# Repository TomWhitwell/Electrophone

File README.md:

# Electrophone

Electrophone is a Eurorack module containing a full-sized single coil guitar pickup.  

This module is a sister to the Mikrophonie Contact Mic Module and Magnetophone Tape Head Module. The Mikrophonie picks up physical vibrations, while Electrophone can hear electromagnetic vibrations. Guitar pickups are designed to convert vibrating metal (strings) into audio, but single coil pickups are also notoriously susceptible to interference of all kinds; hum from transformers, fluorescent lights or even radio signals.

This module is named after the [Epiphone Electrophone](http://www.oldfrets.com/Electrophone.html) an electric guitar from 1935.  

More information: 
- [FAQ](https://github.com/TomWhitwell/Electrophone/wiki/Music-Thing-Electrophone:-FAQ) 
- [BOM](https://github.com/TomWhitwell/Electrophone/wiki/Music-Thing-Elecrophone:-BOM)
- [Troubleshooting](https://github.com/TomWhitwell/Electrophone/wiki/Music-Thing-Electrophone:-Troubleshooting)
- [Demo video at Superbooth 16](https://youtu.be/UVMrQejVZlw?t=3m17s)

Status:  
- August 2016: Finalised circuit 
- May 2016: revised Rev 4 layout trying to get the fuzz circuit to work 
- March 2016: Demonstrated at Superbooth16 in Berlin, with Fuzz circuit bypassed. 
- December 2015: Small component changes in Pickup Board. 
- November 2015: Minor fault in Panel (pickup cutout slightly tight) and major faults in Pickup Board. Rev2 board designed and sent to fab.  
- October 2015: Rev 1 prototype boards sent to fab

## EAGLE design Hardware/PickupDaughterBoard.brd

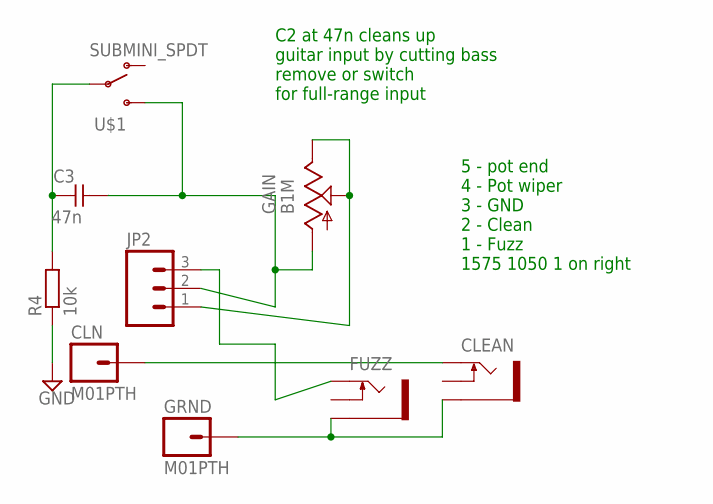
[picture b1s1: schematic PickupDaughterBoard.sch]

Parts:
C3: 47n; C050-024X044
CLEAN: THONKICONNNEW; WQP-PJ301M-12_JACK
CLN: M01PTH; 1X01
FUZZ: THONKICONNNEW; WQP-PJ301M-12_JACK
GAIN: B1M; EVUF
GRND: M01PTH; 1X01
JP2: M03PTH; 1X03
R4: 10k; VERTICAL_RESISTOR
U$1: SUBMINI_SPDT; SUBMINI_TOGGLE

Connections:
CLEAN: CLEAN.P$1_TIP (TIP), CLN.1
END: C3.1, GAIN.1 (A), JP2.2, U$1.3 (S)
FUZZ: FUZZ.P$1_TIP (TIP), JP2.3
GND: CLEAN.P$3_SLEEVE (SLEEVE), FUZZ.P$3_SLEEVE (SLEEVE), GRND.1, R4.1
unnamed: C3.2, R4.2, U$1.COM (COMMON)
WIPER: GAIN.2 (S), GAIN.3 (E), JP2.1

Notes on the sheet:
5 - pot end 4 - Pot wiper 3 - GND 2 - Clean 1 - Fuzz 1575 1050 1 on right
C2 at 47n cleans up guitar input by cutting bass remove or switch for full-range input

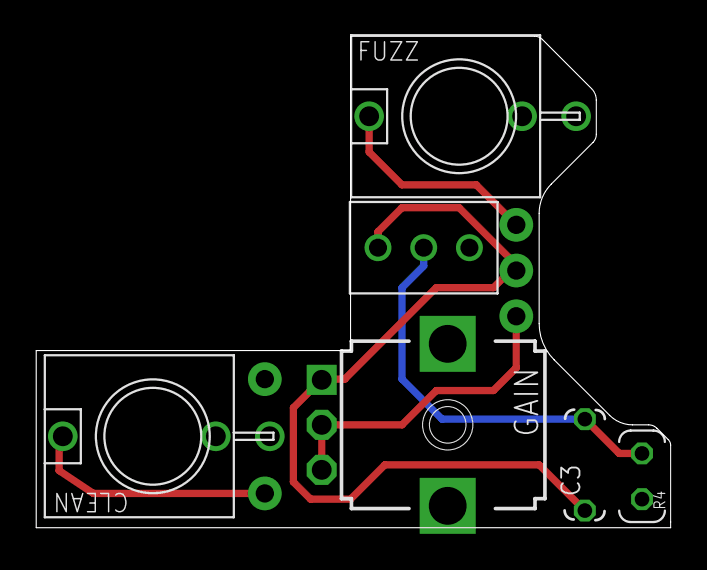
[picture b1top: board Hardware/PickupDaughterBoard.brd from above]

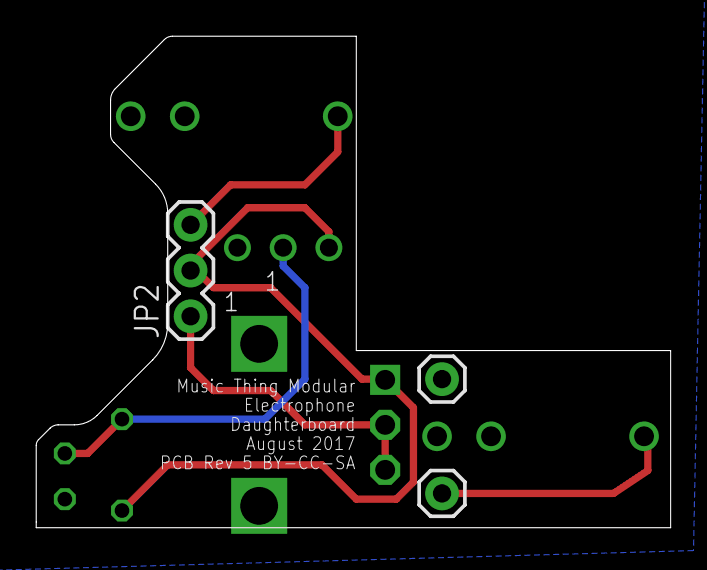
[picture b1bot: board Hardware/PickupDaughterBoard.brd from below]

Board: 2 copper layers, 35.2 x 27.3 mm, 9 parts (3 on the bottom side), 6 nets.

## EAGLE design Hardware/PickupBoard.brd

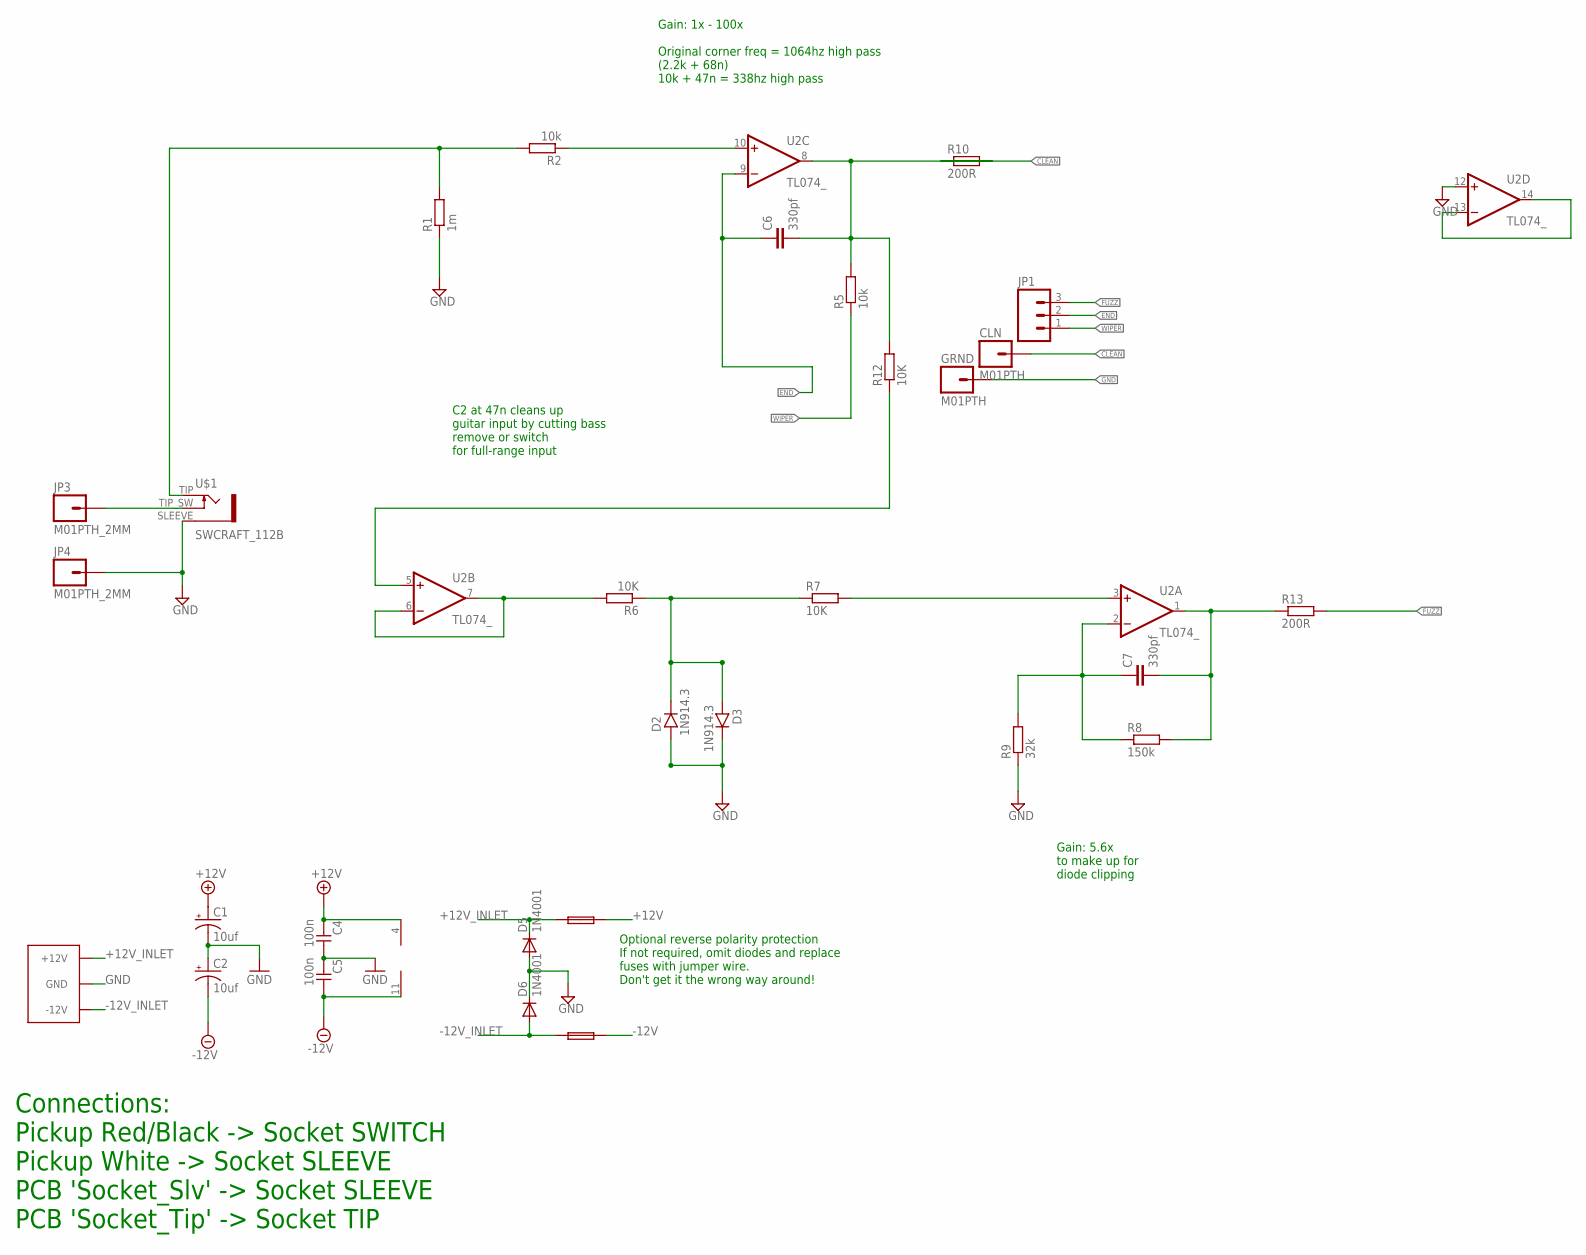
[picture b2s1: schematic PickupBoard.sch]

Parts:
1: FUSE; C050H075X075
C1, C2: 10uf; CPOL-RADIAL-10UF-25V
C4, C5: 100n; C050-024X044
C6, C7: 330pf; 050X030_025
CLN: M01PTH; 1X01
D2, D3: 1N914.3; DO35-3
D5, D6: 1N4001; DO41-10
FUSE: FUSE; C050H075X075
GRND: M01PTH; 1X01
JP1: M03PTH; 1X03
JP3, JP4: M01PTH_2MM; 1X01_2MM
R1: 1m; 7MM_RESISTOR
R2, R5: 10k; 7MM_RESISTOR
R6, R7, R12: 10K; 7MM_RESISTOR
R8: 150k; 7MM_RESISTOR
R9: 32k; 7MM_RESISTOR
R10, R13: 200R; 7MM_RESISTOR
U2: TL074_; DIL14
U$1: SWCRAFT_112B; SWCRAFT_112_SLOTS
U$2: EURO_POWER_LOCK; EURO_PWR_HEADER_LOCK

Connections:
+12V: 1.2, C1.1 (+), C4.2, U2.4 (V+)
+12V_INLET: 1.1, D5.C, U$2.POS1 (+12V), U$2.POS2 (+12V)
-12V: C2.2 (-), C5.1, FUSE.2, U2.11 (V-)
-12V_INLET: D6.A, FUSE.1, U$2.NEG1 (-12V), U$2.NEG2 (-12V)
CLEAN: CLN.1, R10.1
END: C6.1, JP1.2, U2.9 (-IN)
FUZZ: JP1.3, R13.2
GAIN_IN: R1.2, R2.2, U$1.TIP (3)
GND: C1.2 (-), C2.1 (+), C4.1, C5.2, D2.A, D3.C, D5.A, D6.C, GRND.1, JP4.1, R1.1, R9.1, U2.12 (+IN), U$1.SLEEVE (5), U$2.GND1 (GND), U$2.GND2 (GND), U$2.GND3 (GND), U$2.GND4 (GND), U$2.GND5 (GND), U$2.GND6 (GND)
unnamed: R2.1, U2.10 (+IN)
unnamed: U2.13 (-IN), U2.14 (OUT)
unnamed: R7.2, U2.3 (+IN)
unnamed: D2.C, D3.A, R6.1, R7.1
unnamed: C7.1, R8.1, R9.2, U2.2 (-IN)
unnamed: C7.2, R8.2, R13.1, U2.1 (OUT)
unnamed: JP3.1, U$1.TIP_SW (4)
unnamed: C6.2, R5.2, R10.2, R12.2, U2.8 (OUT)
unnamed: R12.1, U2.5 (+IN)
unnamed: R6.2, U2.6 (-IN), U2.7 (OUT)
WIPER: JP1.1, R5.1

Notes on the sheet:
Optional reverse polarity protection If not required, omit diodes and replace fuses with jumper wire. Don't get it the wrong way around!
Connections: Pickup Red/Black -> Socket SWITCH Pickup White -> Socket SLEEVE PCB 'Socket_Slv' -> Socket SLEEVE PCB 'Socket_Tip' -> Socket TIP
Gain: 1x - 100x Original corner freq = 1064hz high pass (2.2k + 68n) 10k + 47n = 338hz high pass
Gain: 5.6x to make up for diode clipping
C2 at 47n cleans up guitar input by cutting bass remove or switch for full-range input

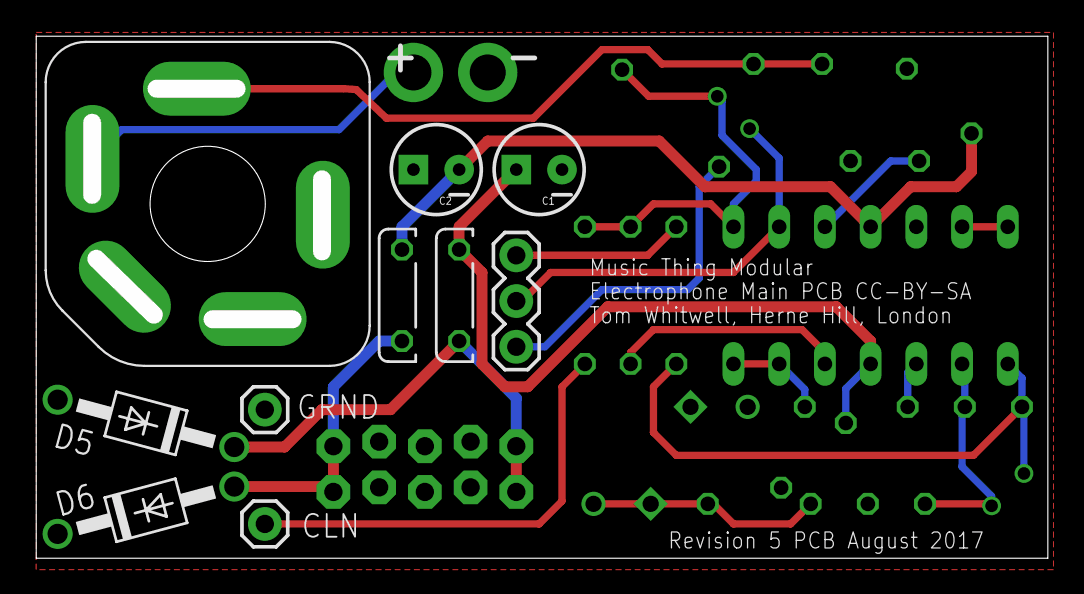
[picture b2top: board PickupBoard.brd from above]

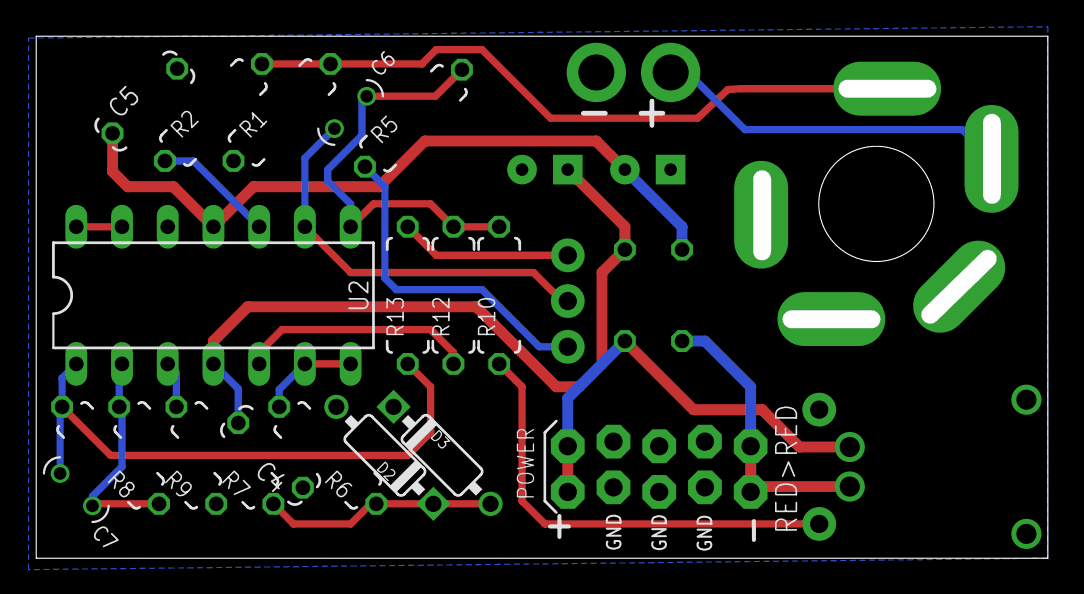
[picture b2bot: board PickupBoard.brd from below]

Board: 4 copper layers, 55.2 x 28.0 mm, 30 parts (20 on the bottom side), 20 nets.

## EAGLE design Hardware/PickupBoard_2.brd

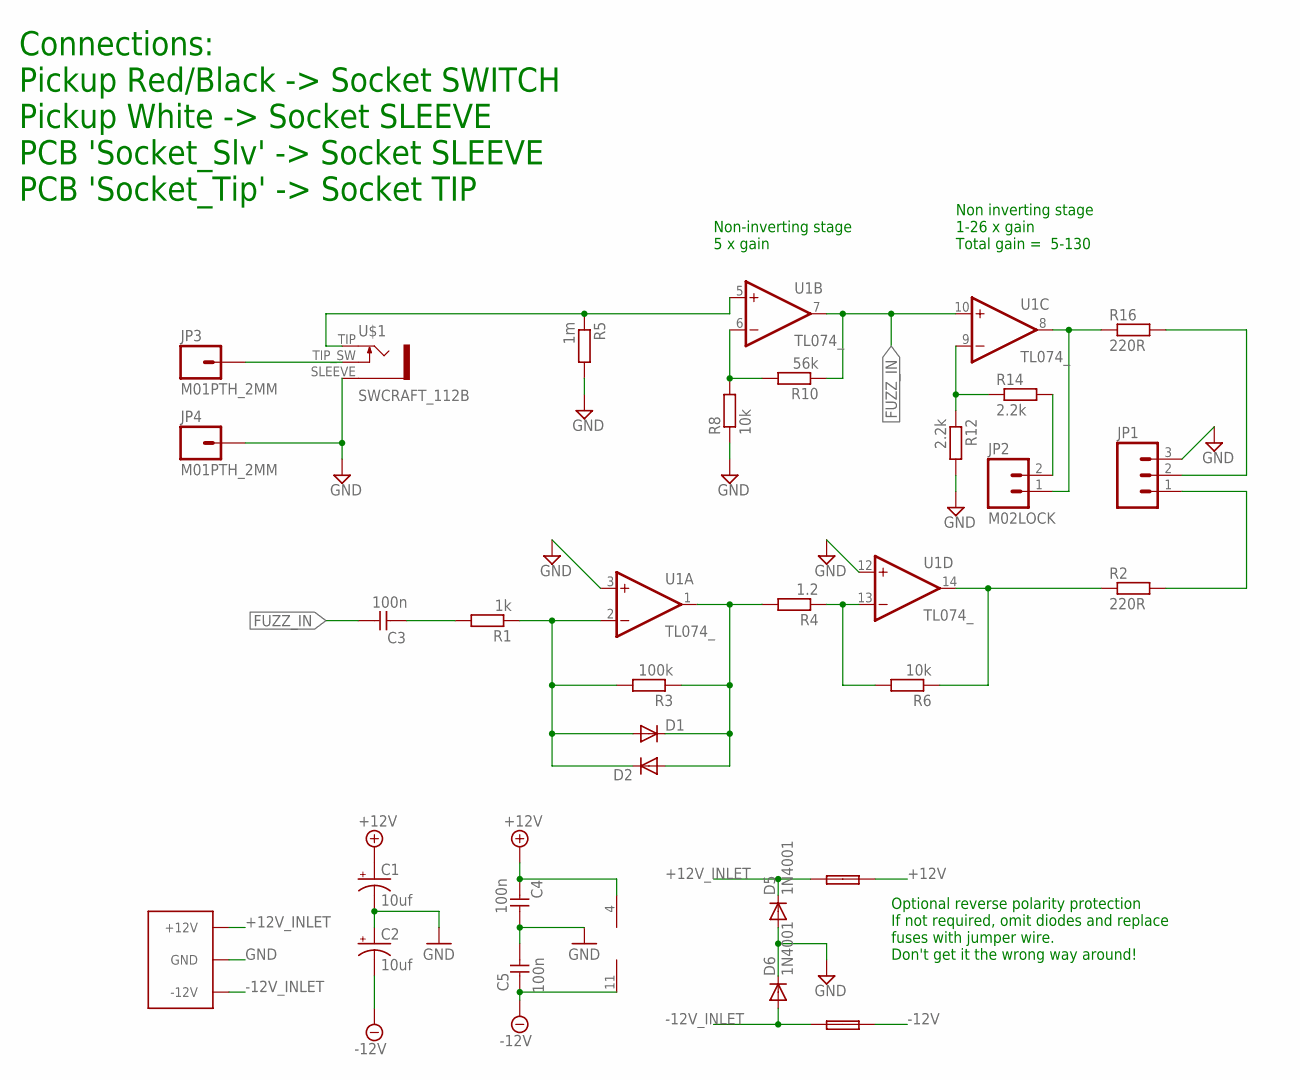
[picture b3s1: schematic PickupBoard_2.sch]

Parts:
1: FUSE; C050H075X075
C1, C2: 10uf; CPOL-RADIAL-10UF-25V
C3, C4, C5: 100n; C050-024X044
D1, D2: SMALL_DIODEDO35-7; DO35-7
D5, D6: 1N4001; DO41-10
FUSE: FUSE; C050H075X075
JP1: M03LOCK; 1X03_LOCK
JP2: M02LOCK; 1X02_LOCK
JP3, JP4: M01PTH_2MM; 1X01_2MM
R1: 1k; 7MM_RESISTOR
R2, R16: 220R; 7MM_RESISTOR
R3: 100k; 7MM_RESISTOR
R4: 1.2; 7MM_RESISTOR
R5: 1m; 7MM_RESISTOR
R6, R8: 10k; 7MM_RESISTOR
R10: 56k; 7MM_RESISTOR
R12, R14: 2.2k; 7MM_RESISTOR
U1: TL074_; DIL14
U$1: SWCRAFT_112B; SWCRAFT_112_SLOTS
U$2: EURO_POWER_LOCK; EURO_PWR_HEADER_LOCK

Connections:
+12V: 1.2, C1.1 (+), C4.2, U1.4 (V+)
+12V_INLET: 1.1, D5.C, U$2.POS1 (+12V), U$2.POS2 (+12V)
-12V: C2.2 (-), C5.2, FUSE.2, U1.11 (V-)
-12V_INLET: D6.A, FUSE.1, U$2.NEG1 (-12V), U$2.NEG2 (-12V)
FUZZ_IN: C3.1, R10.1, U1.7 (OUT), U1.10 (+IN)
GND: C1.2 (-), C2.1 (+), C4.1, C5.1, D5.A, D6.C, JP1.3, JP4.1, R5.2, R8.1, R12.2, U1.3 (+IN), U1.12 (+IN), U$1.SLEEVE (5), U$2.GND1 (GND), U$2.GND2 (GND), U$2.GND3 (GND), U$2.GND4 (GND), U$2.GND5 (GND), U$2.GND6 (GND)
unnamed: R5.1, U1.5 (+IN), U$1.TIP (3)
unnamed: D1.C, D2.A, R3.1, R4.2, U1.1 (OUT)
unnamed: R8.2, R10.2, U1.6 (-IN)
unnamed: D1.A, D2.C, R1.1, R3.2, U1.2 (-IN)
unnamed: JP2.2, R14.2
unnamed: R12.1, R14.1, U1.9 (-IN)
unnamed: C3.2, R1.2
unnamed: JP2.1, R16.1, U1.8 (OUT)
unnamed: R4.1, R6.2, U1.13 (-IN)
unnamed: JP1.2, R16.2
unnamed: R2.1, R6.1, U1.14 (OUT)
unnamed: JP1.1, R2.2
unnamed: JP3.1, U$1.TIP_SW (4)

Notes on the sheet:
Non-inverting stage 5 x gain
Non inverting stage 1-26 x gain Total gain = 5-130
Optional reverse polarity protection If not required, omit diodes and replace fuses with jumper wire. Don't get it the wrong way around!
Connections: Pickup Red/Black -> Socket SWITCH Pickup White -> Socket SLEEVE PCB 'Socket_Slv' -> Socket SLEEVE PCB 'Socket_Tip' -> Socket TIP

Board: 4 copper layers, 29 parts (9 on the bottom side), 19 nets, no tracks yet.

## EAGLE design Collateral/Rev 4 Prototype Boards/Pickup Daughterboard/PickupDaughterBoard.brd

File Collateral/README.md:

#Gerber Files 

These PCB panels are made by manually editing Gerber files using [Cenon](http://www.cenon.info/). The Eagle .brd files will not produce the finished panel designs.

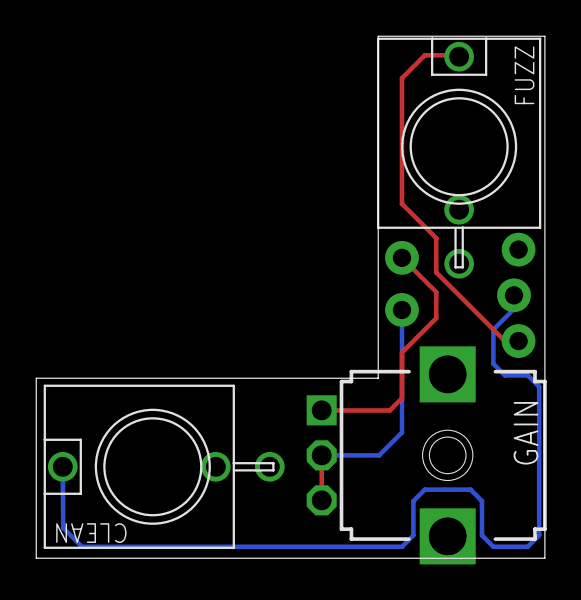
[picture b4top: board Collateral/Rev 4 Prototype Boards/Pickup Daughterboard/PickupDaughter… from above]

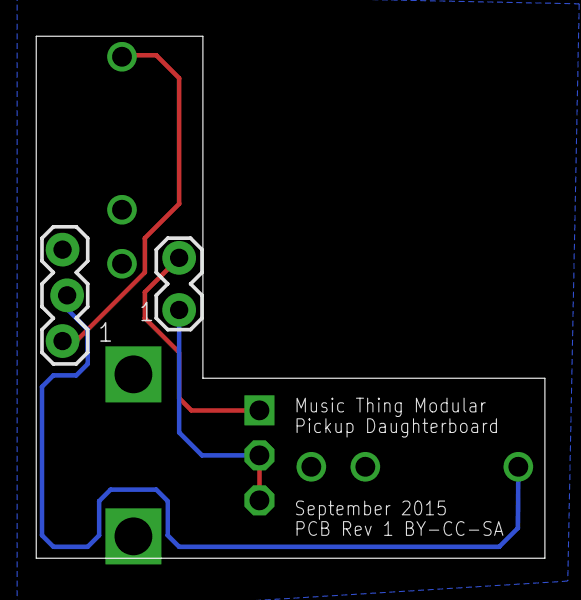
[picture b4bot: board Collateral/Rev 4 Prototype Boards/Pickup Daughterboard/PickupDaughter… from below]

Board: 4 copper layers, 28.3 x 29.0 mm, 5 parts (2 on the bottom side), 5 nets.

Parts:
CLEAN: THONKICONNNEW; WQP-PJ301M-12_JACK
FUZZ: THONKICONNNEW; WQP-PJ301M-12_JACK
GAIN: 50k; EVUF
JP2: M02LOCK; 1X02_LOCK
JP3: 1X03_LOCK

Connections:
GND: CLEAN.P$3_SLEEVE, FUZZ.P$3_SLEEVE, JP3.3
unnamed: FUZZ.P$1_TIP, JP3.1
unnamed: CLEAN.P$1_TIP, JP3.2
unnamed: GAIN.1, JP2.2
unnamed: GAIN.2, GAIN.3, JP2.1

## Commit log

2015-10-01 early board layout
2015-10-01 remove pro
2015-10-03 Building the circuit
2015-10-04 Completed first layout
2015-10-04 First prototypes completed and sent to fab
2015-10-04 Reorganisation
2015-10-05 Hugh Davies article
2015-10-17 add pic
2015-10-18 Simple alt panel
2015-10-19 Grow Pickup cutout
    fixes #1
2015-11-29 New Fuzz Circuit with clipping diodes
    not yet laid out
2015-11-30 Rev2 Pickup Board finished and routed
    Panel and Daughterboard unchanged fixes #2, fixes #3, fixes #4
2015-12-22 notes for changes to fix high frequency oscillation
2015-12-23 Value changes + new cap
2016-01-01 Small routing changes
2016-01-01 Update pickup cutout
2016-04-10 Reworked layout to reduce noise / feedback
2016-05-08 Rev 4 pcb
2016-08-22 Clean up files
2016-08-22 Create Gerbers and Edit
2016-08-22 Rename folder
2016-08-22 Update panel eagle files removing old logos
2016-10-28 Change name on back pcbs
2017-02-27 Remove old Gerber
2017-05-25 First rev5 upload
2017-05-25 roughly on the board not routed
2017-08-03 Designed and routed
2017-08-23 Rev5 with gerbers

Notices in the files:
Hardware/PickupBoard.brd:
Electrophone Main PCB CC-BY-SA
Hardware/PickupBoard_2.brd:
CC-BY-SA Tom Whitwell
parts and their libraries:
SparkFun-Connectors: Licensing: CC v3.0 Share-Alike You are welcome to use this library for commercial purposes.
